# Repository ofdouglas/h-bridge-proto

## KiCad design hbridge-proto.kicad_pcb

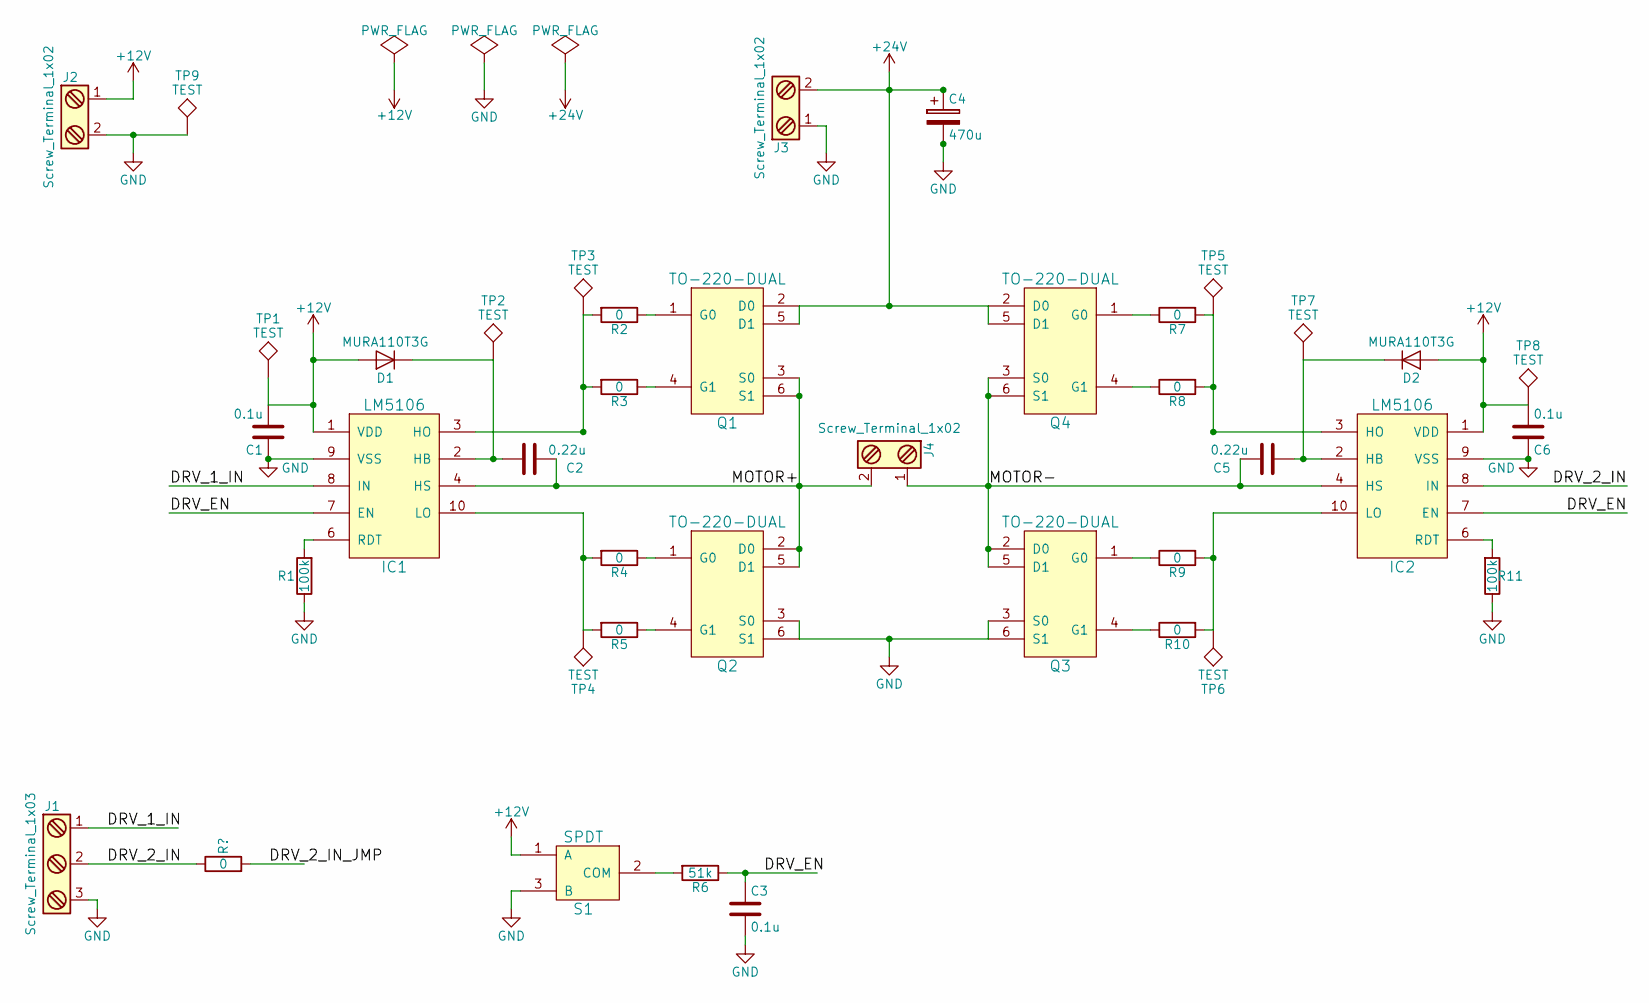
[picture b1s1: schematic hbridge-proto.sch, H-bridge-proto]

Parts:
C1, C3, C6: 0.1u; R_0805_HandSoldering
C2, C5: 0.22u; R_0805_HandSoldering
C4: 470u; CAP_RADIAL_13MM
D1, D2: MURA110T3G; DO-214AC
IC1, IC2: LM5106; MSOP-10_3x3mm_Pitch0.5mm
J1: Screw_Terminal_1x03; mpt_0,5%2f3-2,54
J2: Screw_Terminal_1x02; mpt_0,5%2f2-2,54
J3, J4: Screw_Terminal_1x02; WURTH-2566-2
Q1, Q2, Q3, Q4: TO-220-DUAL; HEATSINK_TO-220_DUAL
R1, R11: 100k; R_0805_HandSoldering
R2, R3, R4, R5, R7, R8, R9, R10: 0; R_0805_HandSoldering
R6: 51k; R_0805_HandSoldering
S1: SPDT; EG1218_SPDT
TP1, TP2, TP3, TP4, TP5, TP6, TP7, TP8: TEST; Measurement_Point_Round-SMD-Pad_Big
TP9: TEST; Measurement_Point_Round-TH_Small

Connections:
+12V: C1.2, C6.2, D1.2 (A), D2.2 (A), IC1.1 (VDD), IC2.1 (VDD), J2.1, S1.1 (A), TP1.1, TP8.1
+24V: C4.1, J3.2, Q1.2 (D0), Q1.5 (D1), Q4.2 (D0), Q4.5 (D1)
/DRV_1_IN: IC1.8 (IN), J1.1
/DRV_EN: C3.1, IC1.7 (EN), IC2.7 (EN), R6.1
/MOTOR+: C2.1, IC1.4 (HS), J4.2, Q1.3 (S0), Q1.6 (S1), Q2.2 (D0), Q2.5 (D1)
/MOTOR-: C5.1, IC2.4 (HS), J4.1, Q3.2 (D0), Q3.5 (D1), Q4.3 (S0), Q4.6 (S1)
GND: C1.1, C3.2, C4.2, C6.1, IC1.9 (VSS), IC2.9 (VSS), J1.3, J2.2, J3.1, Q2.3 (S0), Q2.6 (S1), Q3.3 (S0), Q3.6 (S1), R1.1, R11.1, S1.3 (B), TP9.1
unnamed: C2.2, D1.1 (K), IC1.2 (HB), TP2.1
unnamed: C5.2, D2.1 (K), IC2.2 (HB), TP7.1
unnamed: IC1.3 (HO), R2.2, R3.2, TP3.1
unnamed: IC1.6 (RDT), R1.2
unnamed: IC1.10 (LO), R4.2, R5.2, TP4.1
unnamed: IC2.3 (HO), R7.2, R8.2, TP5.1
unnamed: IC2.6 (RDT), R11.2
unnamed: IC2.10 (LO), R9.2, R10.2, TP6.1
unnamed: Q1.1 (G0), R2.1
unnamed: Q1.4 (G1), R3.1
unnamed: Q2.1 (G0), R4.1
unnamed: Q2.4 (G1), R5.1
unnamed: Q3.1 (G0), R9.1
unnamed: Q3.4 (G1), R10.1
unnamed: Q4.1 (G0), R7.1
unnamed: Q4.4 (G1), R8.1
unnamed: R6.2, S1.2 (COM)

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
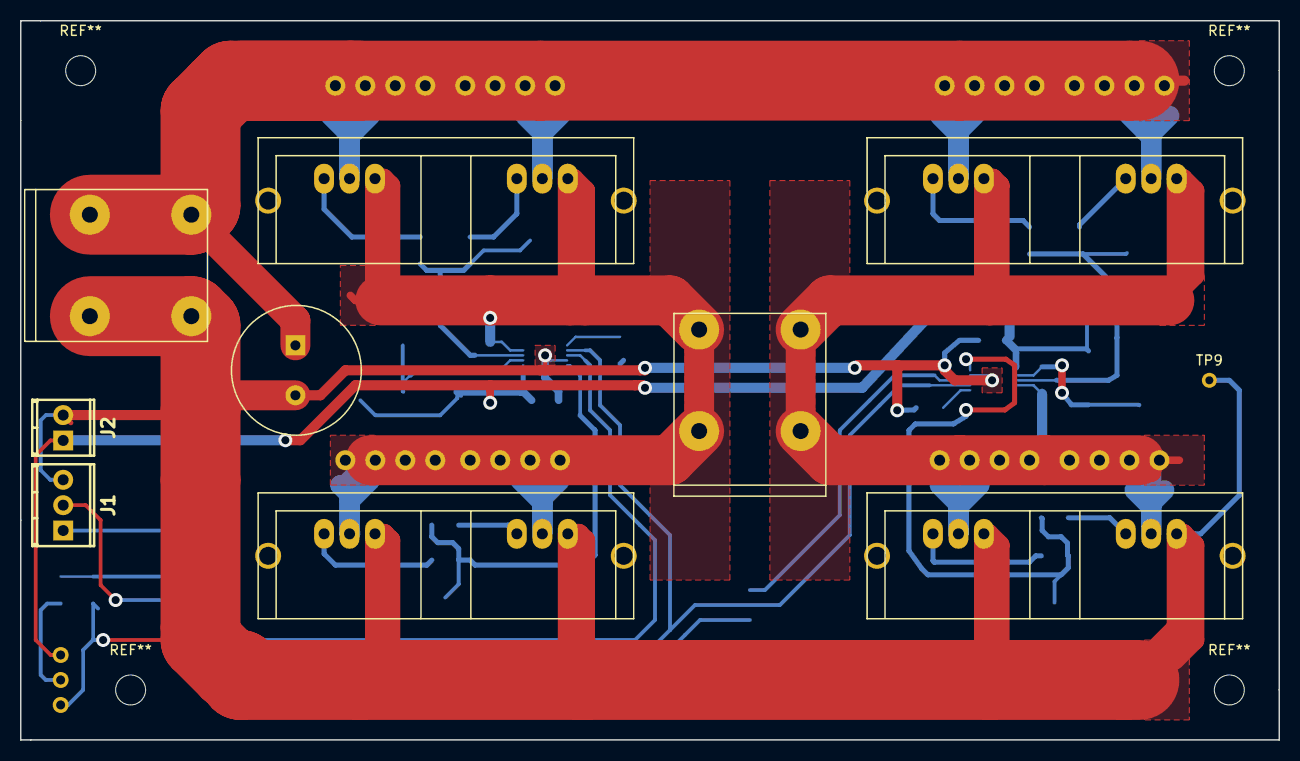
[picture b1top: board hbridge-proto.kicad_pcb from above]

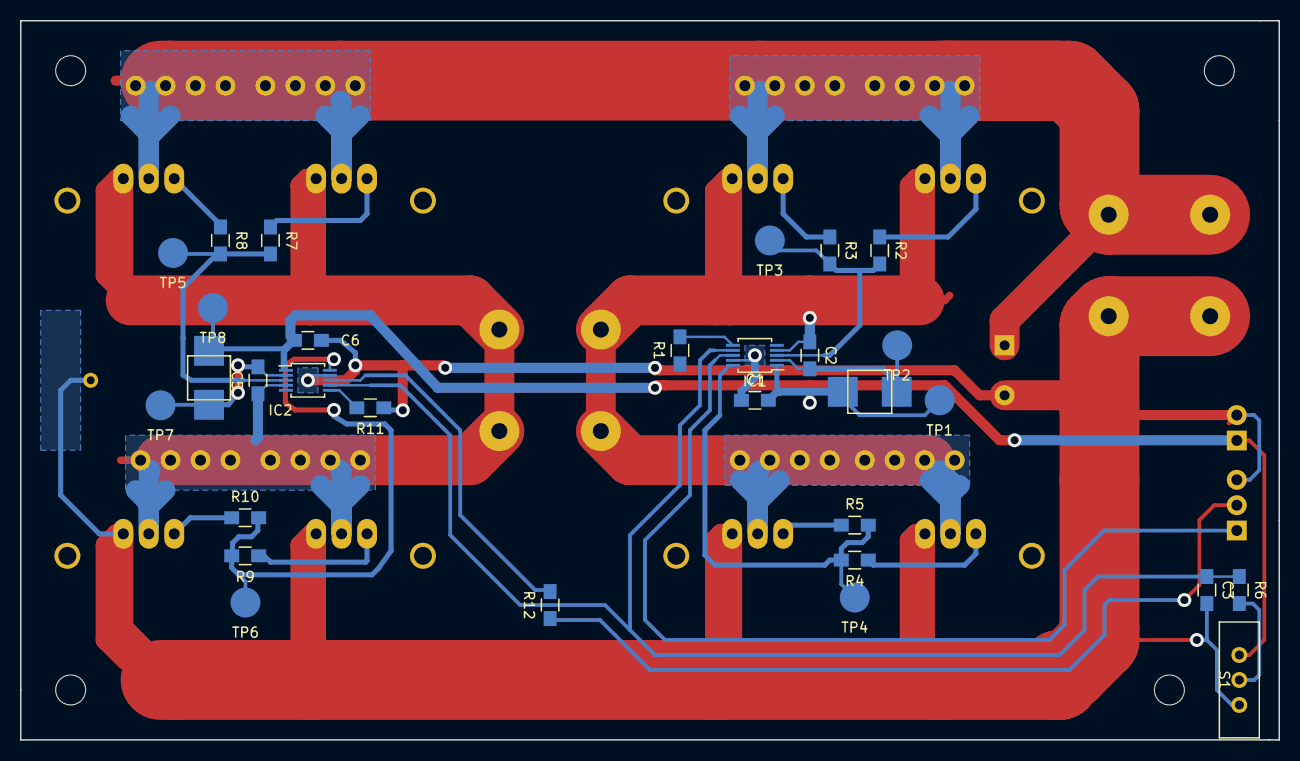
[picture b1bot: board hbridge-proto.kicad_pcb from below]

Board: 2 copper layers, 126.0 x 72.0 mm, 40 parts (30 on the bottom side), 26 nets.

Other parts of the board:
R12: 0; R_0805_HandSoldering

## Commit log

2017-03-23 power trace layout
2017-03-23 first draft complete
2017-03-23 via stitching
2017-03-23 Improved driver signal routing
2017-03-23 final version before via stitching
2017-03-23 version 1 submitted for fab
